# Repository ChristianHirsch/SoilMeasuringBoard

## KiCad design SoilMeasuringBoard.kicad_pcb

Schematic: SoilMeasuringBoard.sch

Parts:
C5: 1u; C_0603_1608Metric
C6, C7: 1n; C_0603_1608Metric
C8: 0.1u; C_0603_1608Metric
D3: LED; LED_0603_1608Metric
D4, D5: BAT54; D_SOD-323
J3: Conn_01x07; PinHeader_1x07_P2.54mm_Vertical
R4: 47; R_0603_1608Metric
R6: 330; R_0603_1608Metric
R7, R8, R9, R10: 1M; R_0603_1608Metric
R11: 4.7k; R_0603_1608Metric
R12, R13, R14: 100k; R_0603_1608Metric
U1: RFD77101; RFDigital_RFD77101
U4: DS18B20U; MSOP-8_3x3mm_P0.65mm
U5: SST26VF016B; SOIC-8_3.9x4.9mm_P1.27mm

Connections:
/BATT_V: U1.21 (P0.05/AIN6); also elsewhere on the board
/BATT_V_EN: U1.12 (P0.17); also elsewhere on the board
/EXCITATION: R6.2, U1.27 (P0.10)
/GPIO0: J3.6, U1.25 (P0.00/AREF0)
/GPIO1: J3.7, U1.23 (P0.01/AIN2)
/LED_1_I: D3.2, U1.31 (P0.06/AREF1/AIN7)
/LED_1_O: R4.2, U1.32 (P0.04/AIN5)
/SENSE_EN: R7.1, R9.1, U1.26 (P0.07)
/SENSE_HIGH: C7.1, D5.1 (K), R9.2, R10.1, U1.22 (P0.03/AIN4)
/SENSE_LOW: C6.1, D4.2 (A), R7.2, R8.1, U1.24 (P0.02/AIN3)
/SENSE_TRACK: D4.1 (K), D5.2 (A), R6.1; also elsewhere on the board
/SPI_MISO: U1.37 (P0.22), U5.2
/SPI_MOSI: U1.33 (P0.20), U5.5
/SPI_SCK: U1.34 (P0.23), U5.6
/SPI_SS: R14.2, U1.38 (P0.25), U5.1
/SWDCLK: J3.5, U1.9 (FACTORY/SWDCLK)
/SWDIO/RESET: J3.4, U1.8 (RESET/SWDIO)
/TEMP_DATA: R11.1, U1.29 (P0.14), U4.1
/TEMP_EN: R11.2, U1.28 (P0.13)
GND: C5.2, C6.2, C7.2, C8.2, J3.1, R8.2, R10.2, U1.1 (GND), U1.2 (GND), U1.4 (GND), U1.6 (GND), U1.19 (GND), U1.30 (GND), U1.42 (GND), U1.43 (GND), U1.44 (GND), U1.45 (GND), U4.4, U4.8, U5.4; also elsewhere on the board
unnamed: D3.1, R4.1
unnamed: R12.2, U5.7
unnamed: R13.2, U5.3
VBUS: J3.3; also elsewhere on the board
VDD: C5.1, C8.1, R12.1, R13.1, R14.1, U1.7 (VDD), U5.8; also elsewhere on the board

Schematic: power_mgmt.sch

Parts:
C1, C2: 4.7u; C_0603_1608Metric
C3, C4: 1u; C_0603_1608Metric
D1, D2: BAT20J; D_SOD-323
J1: USB_B_Micro; USB_Micro-B_Molex_47346-0001
J2: BATT_CONN; JST_PH_S2B-PH-K_1x02_P2.00mm_Horizontal
Q1: Q_NMOS_GSD; SOT-23
Q2, Q3: DMP3099L-13; SOT-23
R1: 3.1k; R_0603_1608Metric
R2: 8.2k; R_0603_1608Metric
R3, R5: 10k; R_0603_1608Metric
U2: MCP73811T-420I-OT; SOT-23-5
U3: TLV74130; SOT-23-5

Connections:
+BATT: C2.1, J2.1, Q2.3 (D), Q3.2 (S), R5.1, U2.3 (VBAT)
/BATT_V: R1.2, R2.1; also elsewhere on the board
/BATT_V_EN: Q1.1 (G); also elsewhere on the board
GND: C1.2, C2.2, C3.2, C4.2, J1.5, J2.2, Q1.2 (S), R2.2, R3.2, U2.2 (VSS), U3.2 (GND); also elsewhere on the board
unnamed: C1.1, D1.2 (A), J1.1, U2.1 (CEN), U2.4 (VDD), U2.5 (PROG)
unnamed: C3.1, D2.1 (K), Q2.2 (S), U3.1 (VIN), U3.3 (EN)
unnamed: Q1.3 (D), Q3.1 (G), R5.2
unnamed: Q3.3 (D), R1.1
VBUS: D1.1 (K), D2.2 (A), Q2.1 (G), R3.1; also elsewhere on the board
VDD: C4.1, U3.5 (VOUT); also elsewhere on the board

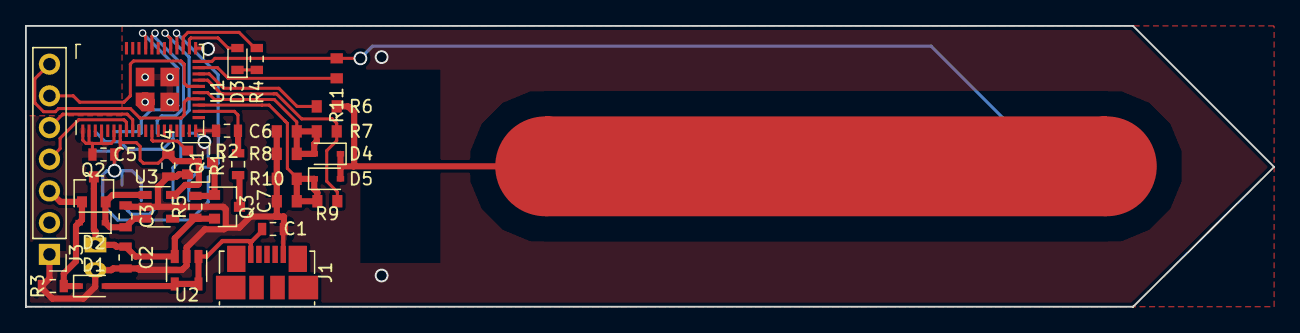
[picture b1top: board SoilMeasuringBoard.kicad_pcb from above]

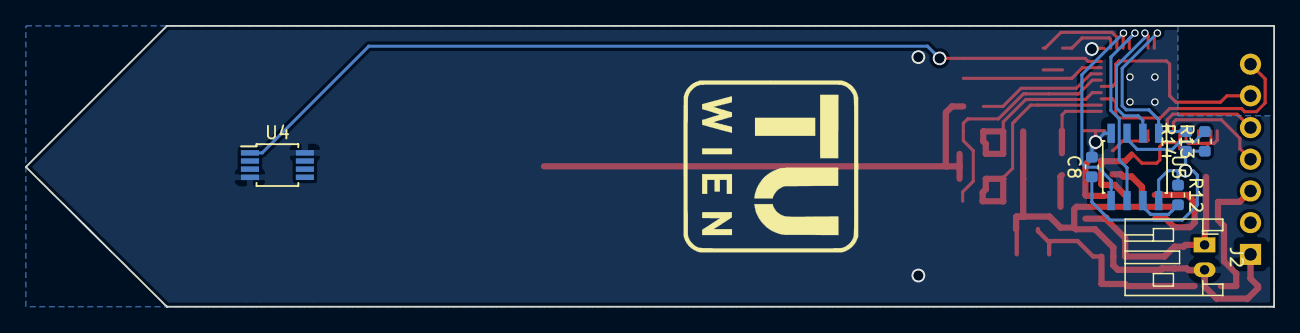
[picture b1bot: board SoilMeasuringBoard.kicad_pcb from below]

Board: 2 copper layers, 100.0 x 22.5 mm, 39 parts (7 on the bottom side), 30 nets.

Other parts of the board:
C***: SENSE; c_layout_1

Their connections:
/SENSE_TRACK: C***.1; also elsewhere on the board

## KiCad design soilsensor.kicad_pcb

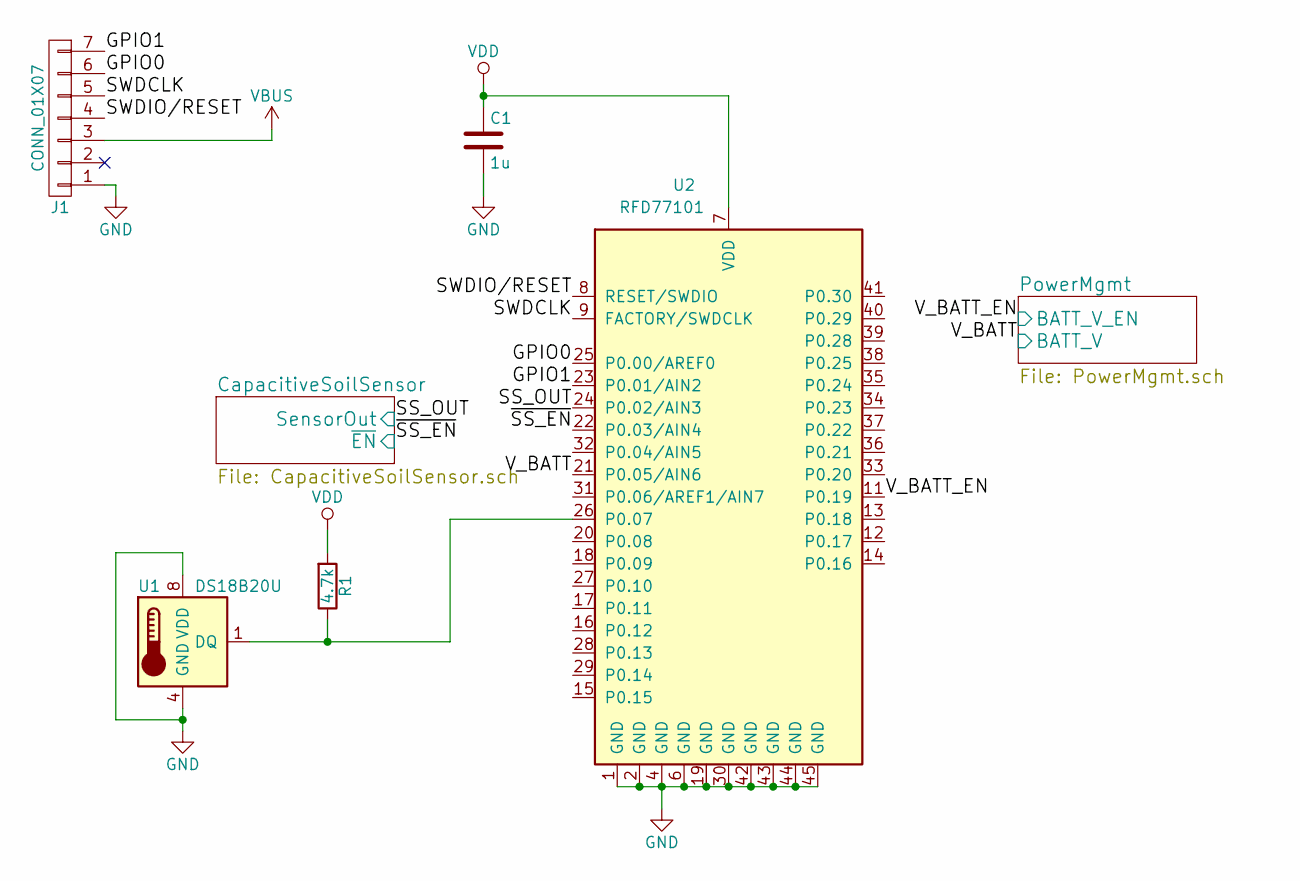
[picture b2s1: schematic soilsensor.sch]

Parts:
C1: 1u; C_0603
J1: CONN_01X07; Pin_Header_Straight_1x07_Pitch2.54mm
R1: 4.7k; R_0603
U1: DS18B20U; MSOP-8_3x3mm_Pitch0.65mm
U2: RFD77101; RFDigital_RFD77101

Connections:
/CapacitiveSoilSensor/SensorOut: U2.24 (P0.02/AIN3); also elsewhere on the board
/CapacitiveSoilSensor/~EN: U2.22 (P0.03/AIN4); also elsewhere on the board
/GPIO0: J1.6, U2.25 (P0.00/AREF0)
/GPIO1: J1.7, U2.23 (P0.01/AIN2)
/PowerMgmt/BATT_V: U2.21 (P0.05/AIN6); also elsewhere on the board
/PowerMgmt/BATT_V_EN: U2.11 (P0.19); also elsewhere on the board
/SWDCLK: J1.5, U2.9 (FACTORY/SWDCLK)
/SWDIO/RESET: J1.4, U2.8 (RESET/SWDIO)
GND: C1.2, J1.1, U1.4 (GND), U1.8 (VDD), U2.1 (GND), U2.2 (GND), U2.4 (GND), U2.6 (GND), U2.19 (GND), U2.30 (GND), U2.42 (GND), U2.43 (GND), U2.44 (GND), U2.45 (GND); also elsewhere on the board
unnamed: R1.1, U1.1 (DQ), U2.26 (P0.07)
VBUS: J1.3; also elsewhere on the board
VDD: C1.1, R1.2, U2.7 (VDD); also elsewhere on the board

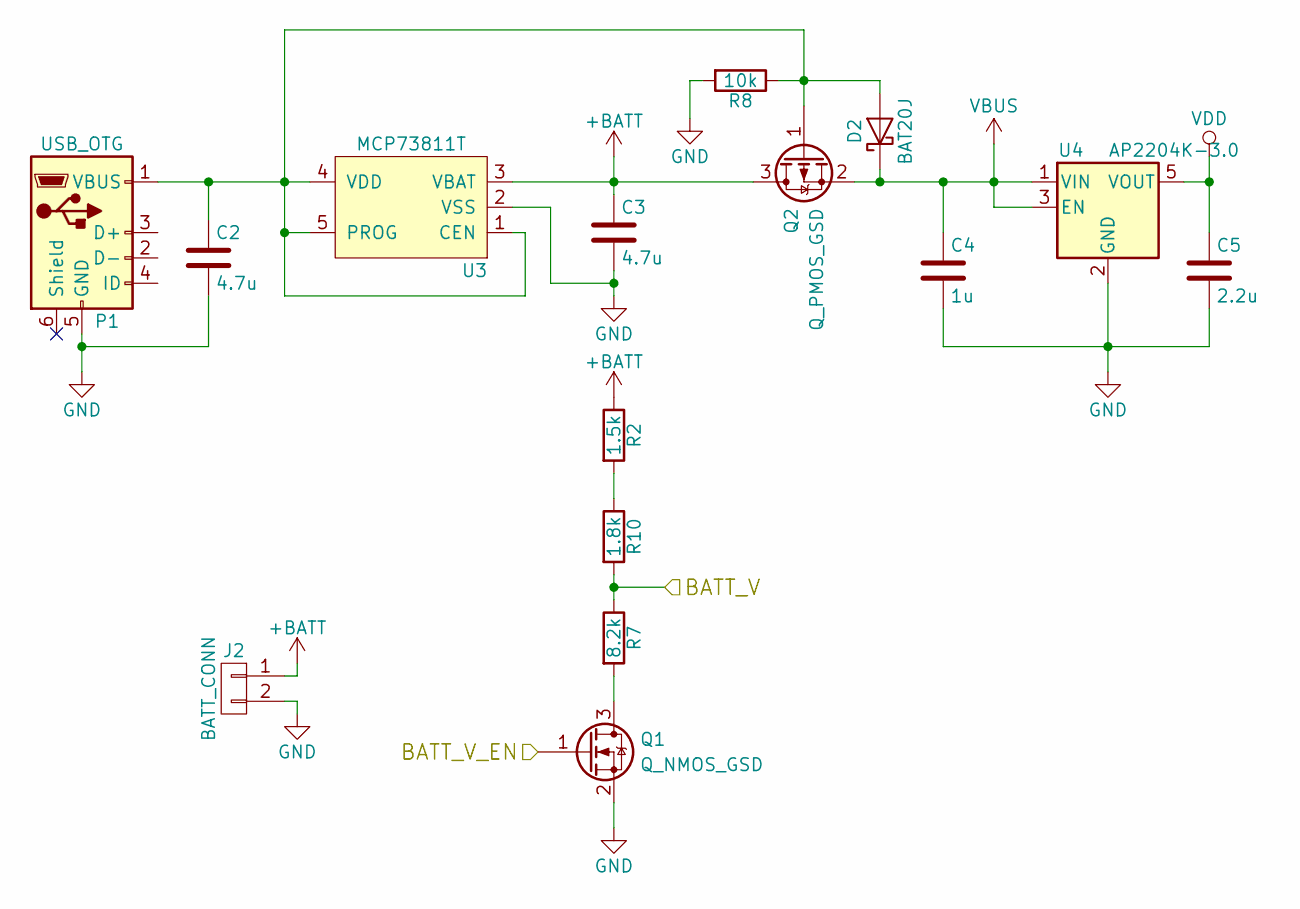
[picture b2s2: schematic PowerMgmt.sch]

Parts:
C2, C3: 4.7u; C_0603
C4: 1u; C_0603
C5: 2.2u; C_0603
D2: BAT20J; SOD-323
J2: BATT_CONN; JST_PH_S2B-PH-K_02x2.00mm_Angled
P1: USB_OTG; USB_Micro-B_Molex_47346-0001
Q1: Q_NMOS_GSD; SOT-23
Q2: Q_PMOS_GSD; SOT-23
R2: 1.5k; R_0603
R7: 8.2k; R_0603
R8: 10k; R_0603
R10: 1.8k; R_0603
U3: MCP73811T; SOT-23-5
U4: AP2204K-3.0; SOT-23-5

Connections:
+BATT: C3.1, J2.1, Q2.3 (D), R2.1, U3.3 (VBAT)
/PowerMgmt/BATT_V: R7.1, R10.2; also elsewhere on the board
/PowerMgmt/BATT_V_EN: Q1.1 (G); also elsewhere on the board
GND: C2.2, C3.2, C4.2, C5.2, J2.2, P1.5 (GND), Q1.2 (S), R8.2, U3.2 (VSS), U4.2 (GND); also elsewhere on the board
unnamed: C2.1, D2.2 (A), P1.1 (VBUS), Q2.1 (G), R8.1, U3.1 (CEN), U3.4 (VDD), U3.5 (PROG)
unnamed: Q1.3 (D), R7.2
unnamed: R2.2, R10.1
VBUS: C4.1, D2.1 (K), Q2.2 (S), U4.1 (VIN), U4.3 (EN); also elsewhere on the board
VDD: C5.1, U4.5 (VOUT); also elsewhere on the board

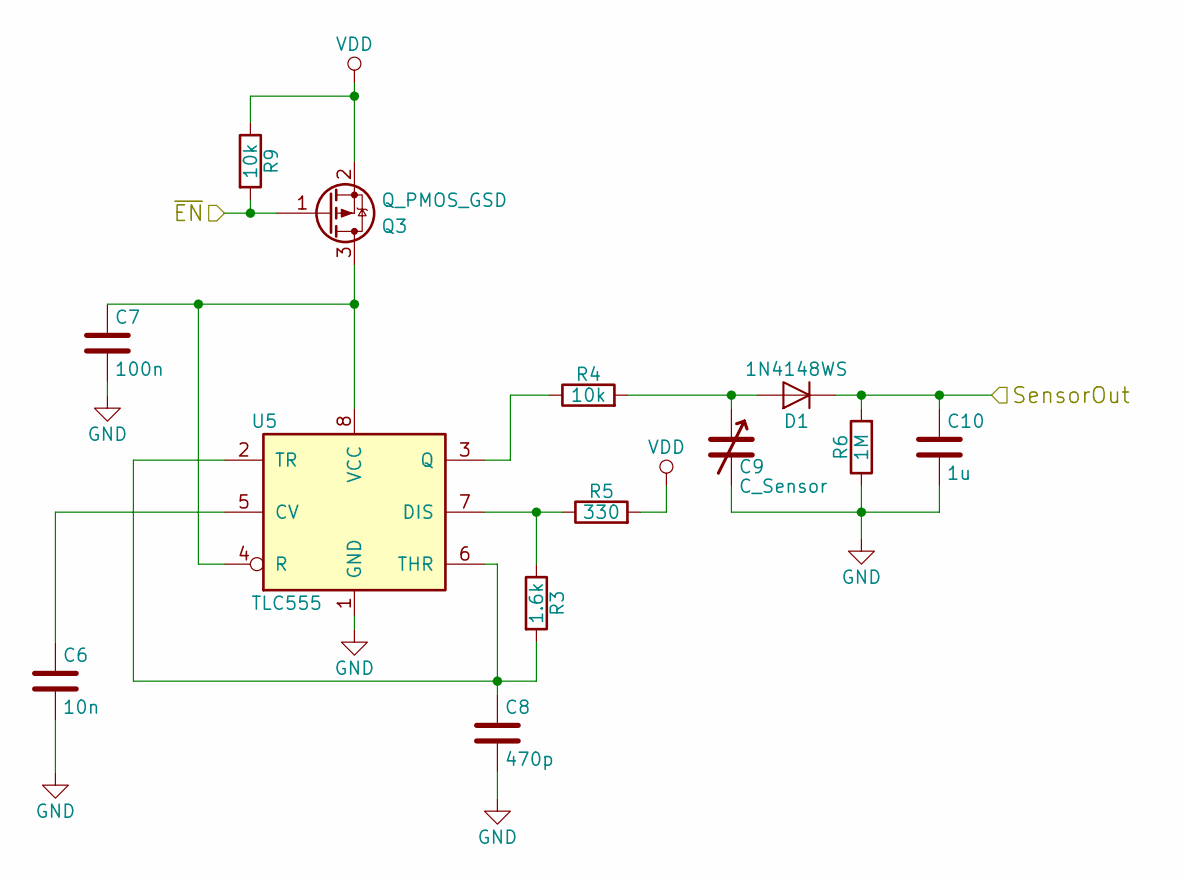
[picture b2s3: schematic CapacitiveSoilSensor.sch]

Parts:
C6: 10n; C_0603
C7: 100n; C_0603
C8: 470p; C_0603
C9: C_Sensor
C10: 1u; C_0603
D1: 1N4148WS; SOD-323
Q3: Q_PMOS_GSD; SOT-23
R3: 1.6k; R_0603
R4, R9: 10k; R_0603
R5: 330; R_0603
R6: 1M; R_0603
U5: TLC555; SOIC-8_3.9x4.9mm_Pitch1.27mm

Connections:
/CapacitiveSoilSensor/SensorOut: C10.1, D1.1 (K), R6.2; also elsewhere on the board
/CapacitiveSoilSensor/~EN: Q3.1 (G), R9.2; also elsewhere on the board
GND: C6.2, C7.2, C8.2, C9.2, C10.2, R6.1, U5.1 (GND); also elsewhere on the board
unnamed: C6.1, U5.5 (CV)
unnamed: C7.1, Q3.3 (D), U5.4 (R), U5.8 (VCC)
unnamed: C8.1, R3.2, U5.2 (TR), U5.6 (THR)
unnamed: C9.1, D1.2 (A), R4.2
unnamed: R3.1, R5.1, U5.7 (DIS)
unnamed: R4.1, U5.3 (Q)
VDD: Q3.2 (S), R5.2, R9.1; also elsewhere on the board

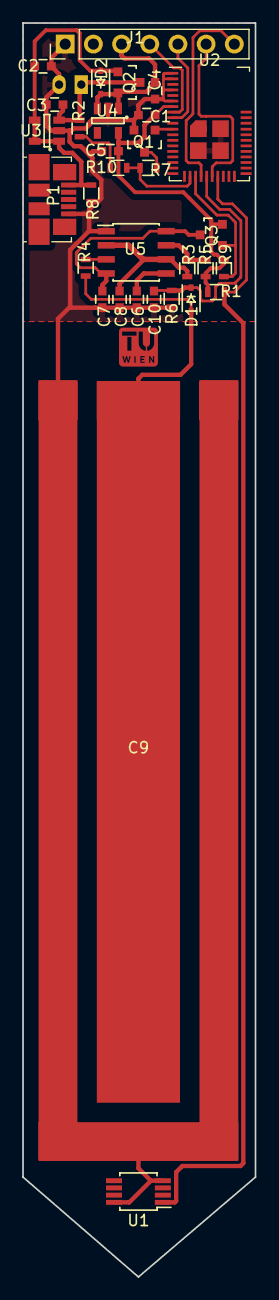
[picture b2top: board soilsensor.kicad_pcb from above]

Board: 2 copper layers, 21.0 x 113.0 mm, 33 parts (1 on the bottom side), 22 nets.

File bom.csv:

Item #,Ref Des,Qty,Manufacturer,Mfg Part #,Description,Package,Type,Supplier,Order Number,unit price,total price
1,U1,1,Maxim Integrated,DS18B20U+,Temperature Sensor,MSOP-8,SMD,mouser.at,700-DS18B20U,"€ 2,310","€ 2,310"
2,U2,1,RFDigital,RFD77101,Simblee Module,LGA-,SMD,mouser.at,975-RFD77101,"€ 17,110","€ 17,110"
3,U3,1,Microchip,MCP73811T-420I/OT,Battery Management Simple Integr Li-Ion /Li-Poly Chrg,SOT-23-5,SMD,mouser.at,579-MCP73811T-420IOT,"€ 0,476","€ 0,476"
4,U4,1,Diodes Incorporated,AP2204K-3.0TRG1,LDO Voltage Regulators LDO CMOS LowCurr,SOT-23-5,SMD,mouser.at,621-AP2204K-3.0TRG1,"€ 0,374","€ 0,374"
5,U5,1,Texas Instruments,TLC555ID,Timer,SOIC-8,SMD,mouser.at,595-TLC555ID,"€ 0,797","€ 0,797"
6,R1,1,,,"4,7k",603,SMD,mouser.at,71-CRCW0603J-4.7K-E3,"€ 0,090","€ 0,090"
7,R2,1,Vishay,CRCW0603J-3.3K-E3,"3,3k",603,SMD,mouser.at,71-CRCW0603J-3.3K-E3,"€ 0,085","€ 0,085"
8,R3,1,,,"1,6k",603,SMD,mouser.at,71-CRCW0603-1.6K-E3,"€ 0,090","€ 0,090"
,"R4, R8, R9",3,,,10k,603,SMD,mouser.at,71-CRCW060310K0JNEB,"€ 0,090","€ 0,270"
,R5,1,,,330,603,SMD,mouser.at,71-CRCW0603J-330-E3,"€ 0,090","€ 0,090"
,R6,1,,,1M,603,SMD,mouser.at,71-CRCW06031M00FKEB,"€ 0,090","€ 0,090"
,R7,1,Vishay,CRCW0603J-8.2K-E3,"8,2k",603,SMD,mouser.at,71-CRCW0603J-8.2K-E3,"€ 0,085","€ 0,085"
,"C1, C4, C10",3,,,1u,603,SMD,mouser.at,581-0603YD105K,"€ 0,090","€ 0,360"
,"C2, C3",2,,,4.7u,603,SMD,mouser.at,81-GRM188R60J475KE9J,"€ 0,098","€ 0,098"
,C5,1,,,2.2u,603,SMD,mouser.at,603-CC603MRX5R5BB225,"€ 0,085","€ 0,085"
,C6,1,,,10n,603,SMD,mouser.at,710-885012206089,"€ 0,040","€ 0,040"
,C7,1,,,100n,603,SMD,mouser.at,581-06033C104K4T4A,"€ 0,036","€ 0,036"
,C8,1,,,470p,603,SMD,mouser.at,710-885012206081,"€ 0,040","€ 0,040"
,D1,1,ON Semi / Fairchild,1N4148WS,Diode,SOD-323,SMD,mouser.at,512-1N4148WS,"€ 0,152","€ 0,152"
,D2,1,STMicroelectronics,BAT20JFILM,Schottky Diode,SOD-323,SMD,mouser.at,511-BAT20JFILM,"€ 0,071","€ 0,071"
,Q1,1,Nexperia,NX7002AKVL,"N MOSFET, 1 Ohm",SOT-23-3,SMD,mouser.at,771-NX7002AKVL,"€ 0,102","€ 0,102"
,"Q2, Q3",1,Diodes Incorporated,DMP3099L-13,MOSFET P-Ch ENH FET -30V 65mOhm -10V -3.8A,SOT-23-3,SMD,mouser.at,621-DMP3099L-13,"€ 0,289","€ 0,588"
,P1,1,Amphenol FCI,10118192-0001LF,USB Connectors 5P MICRO USB TYPE B RECEPTACLE,,SMD,mouser.at,649-10118192-0001LF,"€ 0,376","€ 0,376"
,J1,1,Preci-dip,801-83-006-20-001101,CONN_01x06,,Thru-hole,mouser.at,437-8018300620001101,"€ 0,949","€ 0,949"
,J2,1,JST,S2B-PH-K-S(LF)(SN),Battery Connector,,Thru-hole,digikey.com,455-1719-ND,"€ 0,170","€ 0,170"
,,,,,,,,,,,=SUM(L2:L26)

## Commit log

2017-06-30 initial commit
    add basic kicad files for the soil measuring board
2017-06-30 fix missing regulator, add power mgmt lib
2017-06-30 update power management
    - add battery connector
    - remove unnecessary filter
2017-07-03 add coil sensor layout and footprint
    coil = Capacitive sOIL
2017-07-03 fix minors, make annotations
2017-07-04 add measuring capacitor
2017-07-04 minors
2017-07-04 update gitignore
    remove netlist from ignored files
2017-07-04 add soilsensor.net netlist
2017-07-04 update footprints
2017-07-04 add pcb file
2017-07-06 update capacitive soil sensor layout
2017-07-06 working on pcb
2017-07-19 update capacitive soil measuring sensor
2017-07-19 finish pcb
2017-08-01 easier power mgmt
    use MAX1811 chip
2017-08-01 forget netlist file
2017-08-01 a lot of fixes, finished one-sided layout
2017-08-23 update sensor
2017-10-11 improve power mgmt schematics
2017-10-11 add enable line for cap. sensor
2017-10-11 update schematic for new components
2017-10-11 update pcb for new schematic
2017-10-11 fix power mgmt
2017-10-11 fix cap. soil sensor
2017-10-11 minors in schematic
    rewiring etc.
2017-10-11 create new one-sided pcb
2017-10-16 add bom file
2017-10-16 change mosfet layouts
2017-10-16 add footprints to new mosfets
2017-10-16 update pcb with new mosfets
2017-10-16 update total cost in bom file
2017-11-07 update power mgmt
2017-11-07 update bom
2017-11-07 update schematics
2017-11-07 update pcb
2017-11-07 add cache lib
2017-11-07 add new layout for soil measuring capacity
2017-11-07 add TU Wien logo
2017-11-07 update project
2017-12-07 fix #3: rewire p mosfet to swicht c-sensor
2018-04-17 update houding, add new capacitive layout
2018-04-17 cleanup for new version
2018-08-01 pre-flash commit
2018-08-01 add flash memory
2018-11-08 update README w/ schematic
2019-05-31 final fixes
